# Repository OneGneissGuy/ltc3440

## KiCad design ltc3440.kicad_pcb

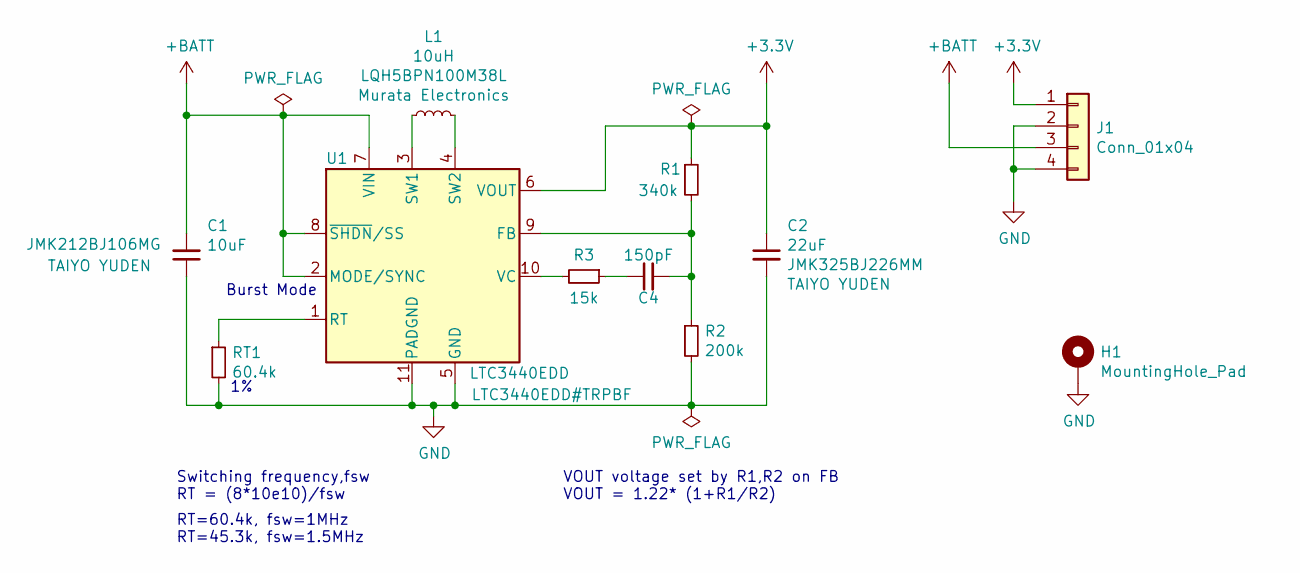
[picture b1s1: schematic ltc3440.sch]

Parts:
C1: 10uF; C_1206_3216Metric; MPN JMK212BJ106MG
C2: 22uF; C_1206_3216Metric; MPN JMK325BJ226MM
C4: 150pF; C_0603_1608Metric_Pad1.05x0.95mm_HandSolder
H1: MountingHole_Pad; MountingHole_2.2mm_M2
J1: Conn_01x04; PinSocket_1x04_P2.54mm_Vertical
L1: 10uH; IND_LQH5BPN100M38L; MPN LQH5BPN100M38L; Digikey_PN 490-16631-1-ND
R1: 340k; R_0603_1608Metric_Pad1.05x0.95mm_HandSolder
R2: 200k; R_0603_1608Metric_Pad1.05x0.95mm_HandSolder
R3: 15k; R_0603_1608Metric_Pad1.05x0.95mm_HandSolder
RT1: 60.4k; R_0603_1608Metric_Pad1.05x0.95mm_HandSolder
U1: LTC3440EDD; DFN-10-1EP_3x3mm_P0.5mm_EP1.65x2.38mm; MPN LTC3440EDD#TRPBF; Digikey_PN LTC3440EDD#TRPBFCT-ND

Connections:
+3V3: C2.1, J1.1, R1.1, U1.6 (VOUT)
+BATT: C1.2, J1.3, U1.2 (MODE/SYNC), U1.7 (VIN), U1.8 (~SHDN~/SS)
GND: C1.1, C2.2, H1.1, J1.2, J1.4, R2.2, RT1.2, U1.5 (GND), U1.11 (PADGND)
unnamed: C4.1, R3.1
unnamed: C4.2, R1.2, R2.1, U1.9 (FB)
unnamed: L1.1, U1.3 (SW1)
unnamed: L1.2, U1.4 (SW2)
unnamed: R3.2, U1.10 (VC)
unnamed: RT1.1, U1.1 (RT)

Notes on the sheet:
VOUT voltage set by R1,R2 on FB VOUT = 1.22* (1+R1/R2)
Switching frequency,fsw RT = (8*10e10)/fsw
RT=60.4k, fsw=1MHz RT=45.3k, fsw=1.5MHz
Burst Mode

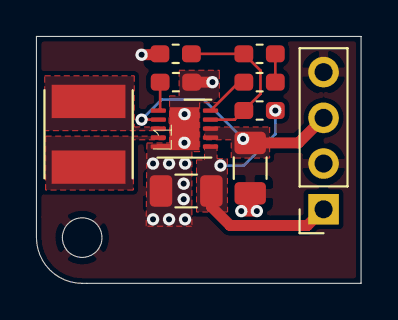
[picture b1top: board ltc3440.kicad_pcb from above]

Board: 2 copper layers, 18.0 x 13.7 mm, 11 parts (0 on the bottom side), 9 nets.

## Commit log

2020-09-23 init commit
2020-09-23 fix 1.5 mhz rt val
2020-09-23 adds L1 val
2020-09-23 update to follow application from datasheet page1
2020-09-23 adds footprints
2020-09-23 layout board
2020-09-23 adds gitignore and readme
2020-09-23 updates symbols for consistency
2020-09-23 update gitignore
2020-09-23 Remove ignored files
2020-09-24 add inductor 3d model and adjust cu pours
2020-09-24 change to burst mode
2020-09-27 change inductor with smaller footprint
2020-10-01 fix error sw2 to vout
2020-10-01 reduce board size
